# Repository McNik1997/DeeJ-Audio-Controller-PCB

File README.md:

I designed my own pcb for a 5-slider deej project. I already use Version 1.0 but I also created Version 1.1 with static leds for lighting decals.

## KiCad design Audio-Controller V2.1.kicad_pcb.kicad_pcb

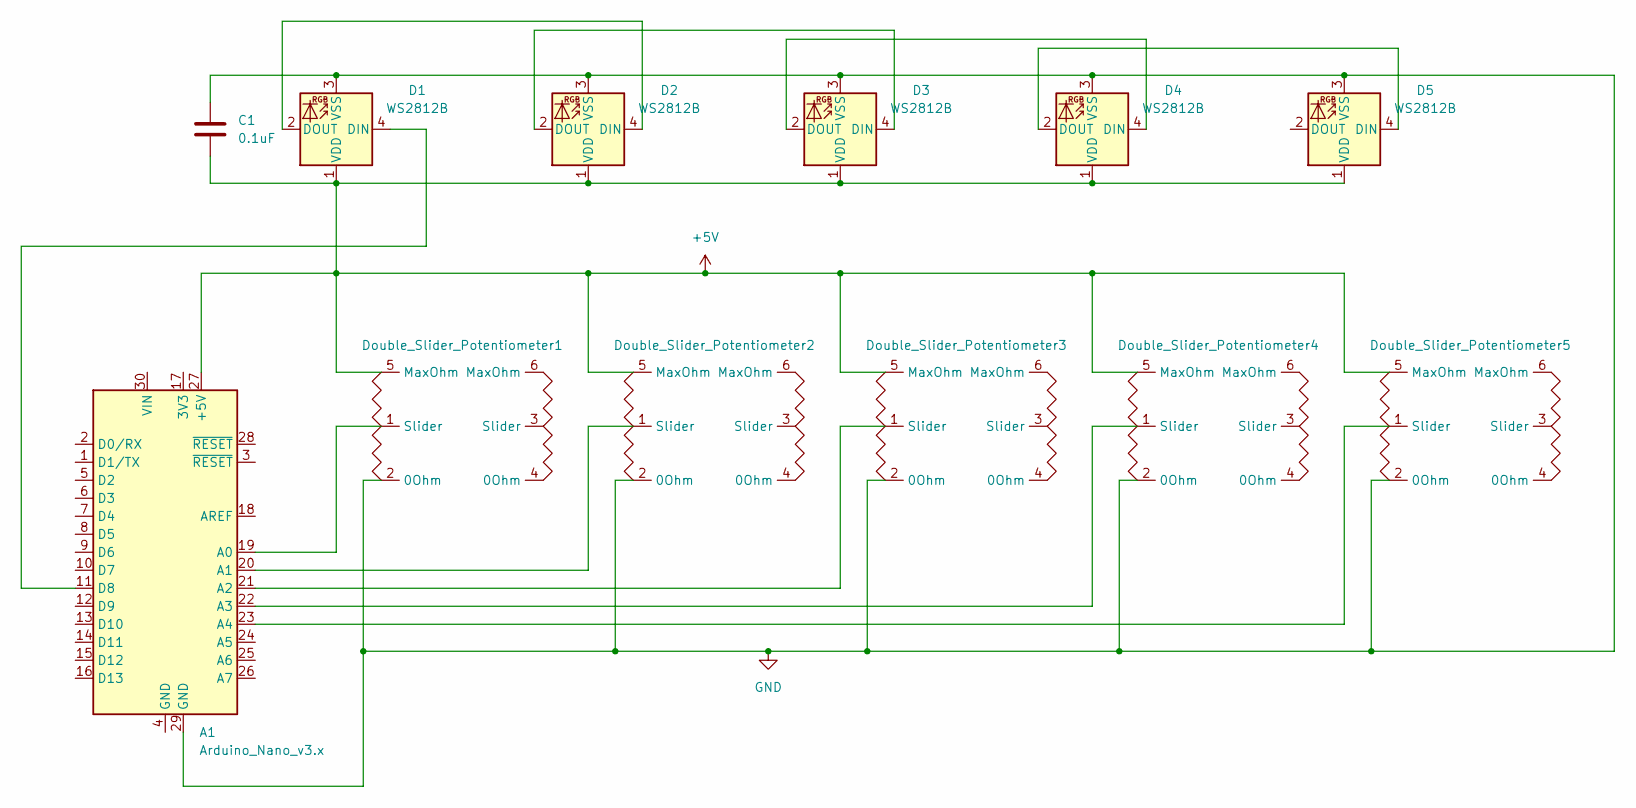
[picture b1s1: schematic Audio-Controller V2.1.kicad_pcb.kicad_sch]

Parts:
A1: Arduino_Nano_v3.x; Arduino_Nano
C1: 0.1uF; C_1206_3216Metric_Pad1.33x1.80mm_HandSolder
D1, D2, D3, D4, D5: WS2812B; LED_WS2812B_PLCC4_5.0x5.0mm_P3.2mm
Double_Slider_Potentiometer1, Double_Slider_Potentiometer2, Double_Slider_Potentiometer3, Double_Slider_Potentiometer4, Double_Slider_Potentiometer5: Potentiometer B103 Slider 75x9.1mm

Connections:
+5V: A1.27 (+5V), C1.2, D1.1 (VDD), D2.1 (VDD), D3.1 (VDD), D4.1 (VDD), D5.1 (VDD), Double_Slider_Potentiometer1.5 (MaxOhm), Double_Slider_Potentiometer2.5 (MaxOhm), Double_Slider_Potentiometer3.5 (MaxOhm), Double_Slider_Potentiometer4.5 (MaxOhm), Double_Slider_Potentiometer5.5 (MaxOhm)
GND: A1.29 (GND), C1.1, D1.3 (VSS), D2.3 (VSS), D3.3 (VSS), D4.3 (VSS), D5.3 (VSS), Double_Slider_Potentiometer1.2 (0Ohm), Double_Slider_Potentiometer2.2 (0Ohm), Double_Slider_Potentiometer3.2 (0Ohm), Double_Slider_Potentiometer4.2 (0Ohm), Double_Slider_Potentiometer5.2 (0Ohm)
unnamed: A1.19 (A0), Double_Slider_Potentiometer1.1 (Slider)
unnamed: A1.20 (A1), Double_Slider_Potentiometer2.1 (Slider)
unnamed: A1.21 (A2), Double_Slider_Potentiometer3.1 (Slider)
unnamed: A1.22 (A3), Double_Slider_Potentiometer4.1 (Slider)
unnamed: A1.23 (A4), Double_Slider_Potentiometer5.1 (Slider)
unnamed: A1.11 (D8), D1.4 (DIN)
unnamed: D1.2 (DOUT), D2.4 (DIN)
unnamed: D2.2 (DOUT), D3.4 (DIN)
unnamed: D3.2 (DOUT), D4.4 (DIN)
unnamed: D4.2 (DOUT), D5.4 (DIN)

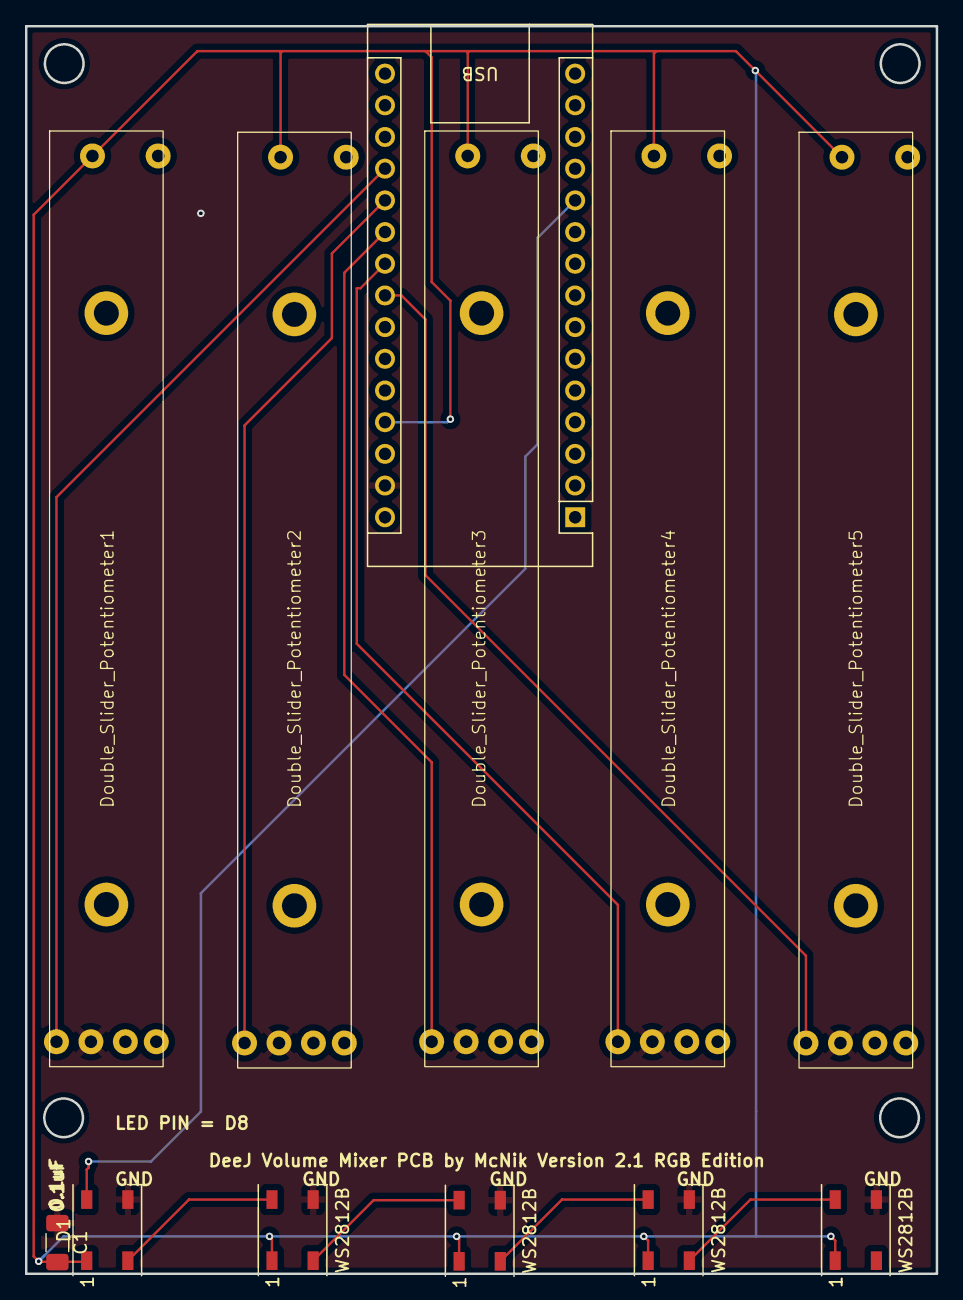
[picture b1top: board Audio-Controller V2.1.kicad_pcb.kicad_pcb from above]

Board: 2 copper layers, 73.0 x 100.0 mm, 12 parts (0 on the bottom side), 12 nets.

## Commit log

2024-07-03 Version 1.0
    Confirmed working PCB for 5 Sliders
2024-07-03 Version 1.1
    Added static leds below the decals.
2024-07-03 Version 1.1
    File cleanup
2024-07-04 Version 2.0 RGB Edition
2024-07-04 Version 2.0
2024-07-15 Version 2.1
    Fixed errors and tested design.
    Working code included.
2024-07-15 small corrections
2024-07-15 tidying up
2024-07-15 Errors found and resolved
2025-01-21 Included missing lid
